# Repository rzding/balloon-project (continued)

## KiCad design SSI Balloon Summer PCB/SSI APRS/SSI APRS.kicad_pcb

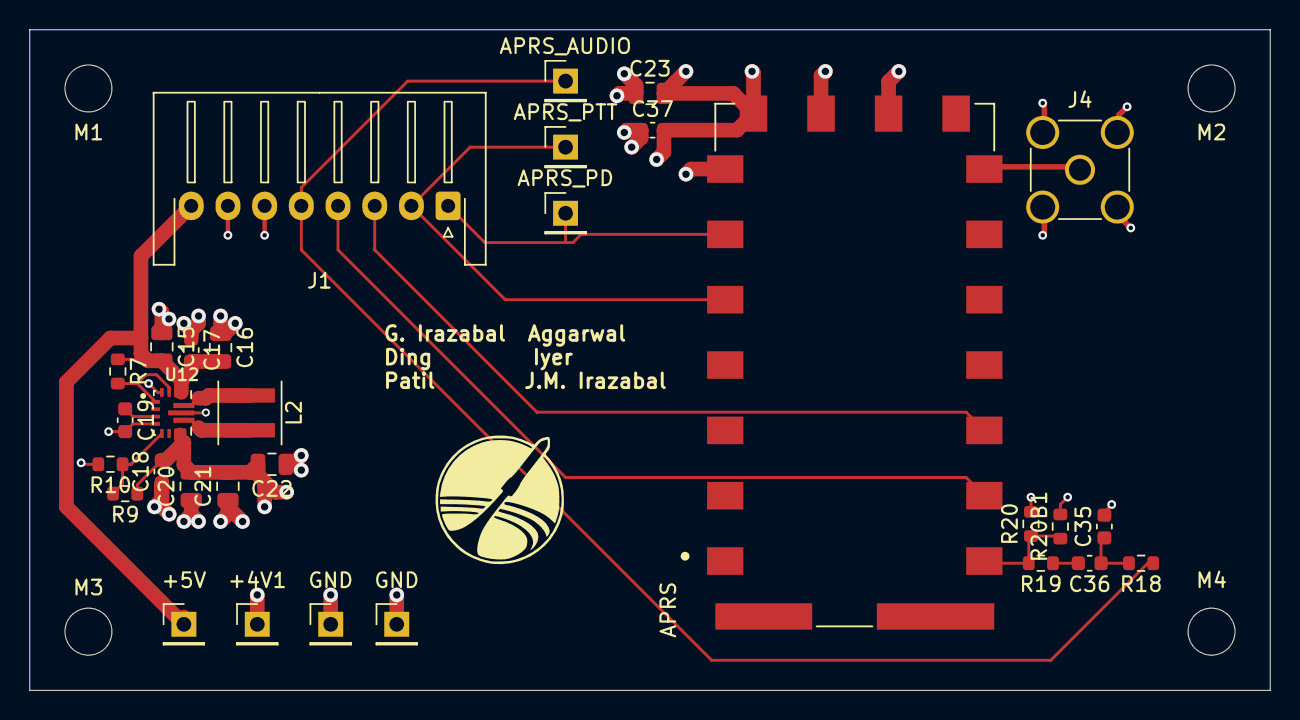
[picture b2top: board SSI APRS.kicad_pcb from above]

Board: 4 copper layers, 84.5 x 45.0 mm, 35 parts (0 on the bottom side), 17 nets.

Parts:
+4V1, +5V: Conn_01x01; PinHeader_1x01_P2.54mm_Vertical
APRS: DRA818V; DORJI_DRA818V
APRS_AUDIO: Conn_01x01; PinHeader_1x01_P2.54mm_Vertical
APRS_PD: Conn_01x01; PinHeader_1x01_P2.54mm_Vertical
APRS_PTT: Conn_01x01; PinHeader_1x01_P2.54mm_Vertical
C15, C16, C23: 10uF; C_0805_2012Metric
C17, C18: 10uF; C_0603_1608Metric
C19, C36, C37: 100nF; C_0603_1608Metric
C20, C21, C22: 22uF; C_0805_2012Metric
C35: 10nF; C_0603_1608Metric
GND: Conn_01x01; PinHeader_1x01_P2.54mm_Vertical
GND#2: Conn_01x01; PinHeader_1x01_P2.54mm_Vertical
J1: Conn_01x08; JST_XH_S8B-XH-A-1_1x08_P2.50mm_Horizontal
J4: APRS antenna; SMA_Amphenol_901-144_Vertical
L2: 1.5 uH; L_Coilcraft_XxL4020
M1, M2, M3, M4: MountingHole_3.2mm_M3
R7, R19: 10k; R_0603_1608Metric
R9: 510k; R_0603_1608Metric
R10: 120k; R_0603_1608Metric
R18: 1k; R_0603_1608Metric
R20: 470; R_0603_1608Metric
R20B1: TBD; R_0603_1608Metric
U12: TPS63070RNMR; VREG_TPS63070RNMR

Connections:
+4V1: +4V1.1 (Pin_1_1), APRS.8 (VBAT), C18.2, C20.2, C21.2, C22.2, C23.2, C37.2, R9.1, U12.7_8 (VOUT)
+5V: +5V.1 (Pin_1_1), C15.2, C16.2, C17.2, J1.8, R7.1, U12.12_13 (VIN)
/APRS_AUDIO: APRS_AUDIO.1 (Pin_1_1), J1.5, R18.1
/APRS_PD: APRS.6 (PD), APRS_PD.1 (Pin_1_1), J1.1
/APRS_PTT: APRS.5 (PTT), APRS_PTT.1 (Pin_1_1), J1.2
/APRS_RX: APRS.16 (RXD), J1.3
/APRS_TX: APRS.17 (TXD), J1.4
GND: APRS.7 (H/L), APRS.9 (GND), APRS.10 (GND), C15.1, C16.1, C17.1, C18.1, C19.2, C20.1, C21.1, C22.1, C23.1, C35.2, C37.1, GND.1 (Pin_1_1), GND#2.1 (Pin_1_1), J1.6, J1.7, J4.2 (Ext), R10.2, R20.2, R20B1.2, U12.4 (GND), U12.10 (PGND), U12.15 (VSEL)
unnamed: C35.1, C36.1, R18.2
unnamed: C36.2, R19.1
unnamed: APRS.12 (ANT), J4.1 (In)
unnamed: APRS.18 (MIC_IN), R19.2, R20.1, R20B1.1
unnamed: R7.2, U12.1 (PS/SYNC), U12.14 (EN)
unnamed: R9.2, R10.1, U12.5 (FB)
unnamed: L2.1, U12.11 (L1)
unnamed: L2.2, U12.9 (L2)
unnamed: C19.1, U12.3 (VAUX)

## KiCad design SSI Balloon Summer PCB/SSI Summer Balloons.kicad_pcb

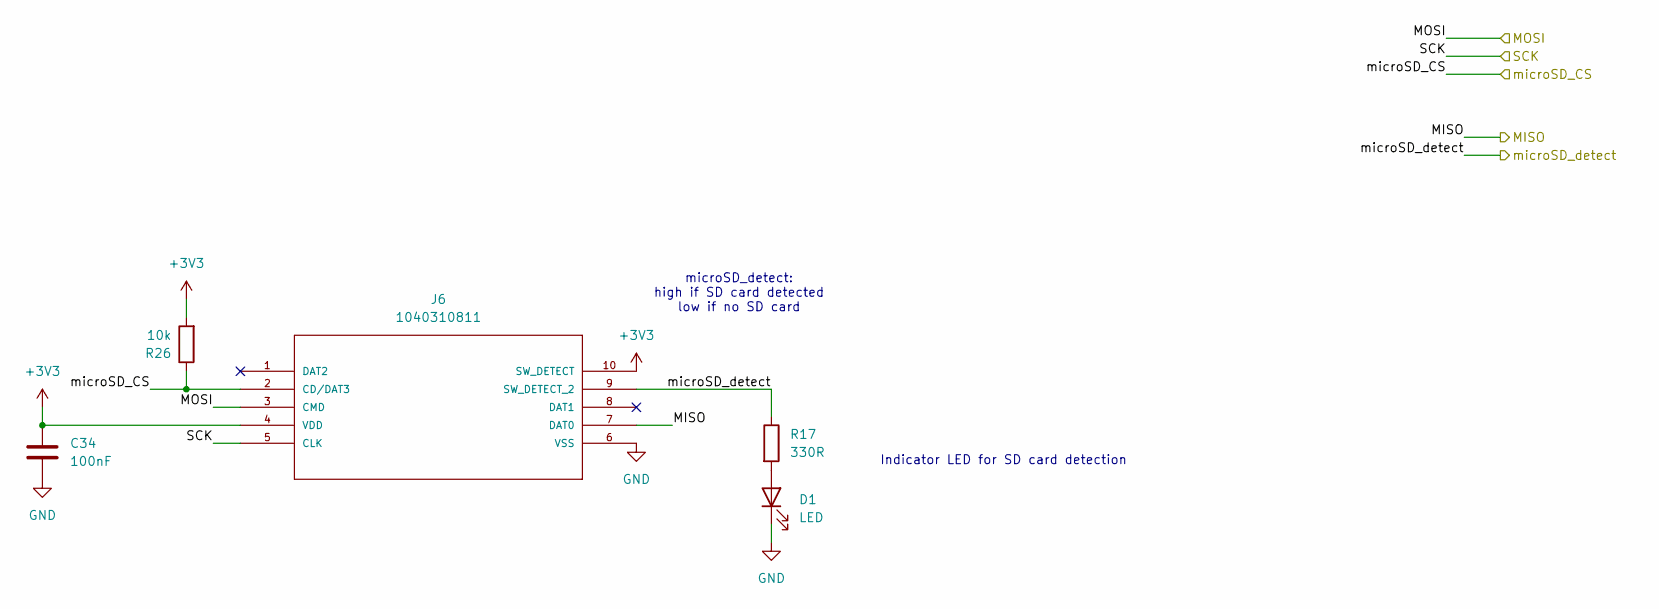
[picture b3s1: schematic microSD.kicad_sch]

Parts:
C34: 100nF
D1: LED
J6: 1040310811; 104031-0811_MOL; MANUFACTURER_PART_NUMBER 1040310811
R17: 330R
R26: 10k

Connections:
+3V3: C34.1, J6.4 (VDD), J6.10 (SW_DETECT), R26.2; also elsewhere on the board
/MCU (STM)/MISO: J6.7 (DAT0); also elsewhere on the board
/MCU (STM)/MOSI: J6.3 (CMD); also elsewhere on the board
/MCU (STM)/SCK: J6.5 (CLK); also elsewhere on the board
/MCU (STM)/microSD_CS: J6.2 (CD/DAT3), R26.1; also elsewhere on the board
/MCU (STM)/microSD_detect: J6.9 (SW_DETECT_2), R17.1; also elsewhere on the board
GND: C34.2, D1.1 (K), J6.6 (VSS); also elsewhere on the board
unnamed: D1.2 (A), R17.2

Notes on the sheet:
microSD_detect: high if SD card detected low if no SD card
Indicator LED for SD card detection

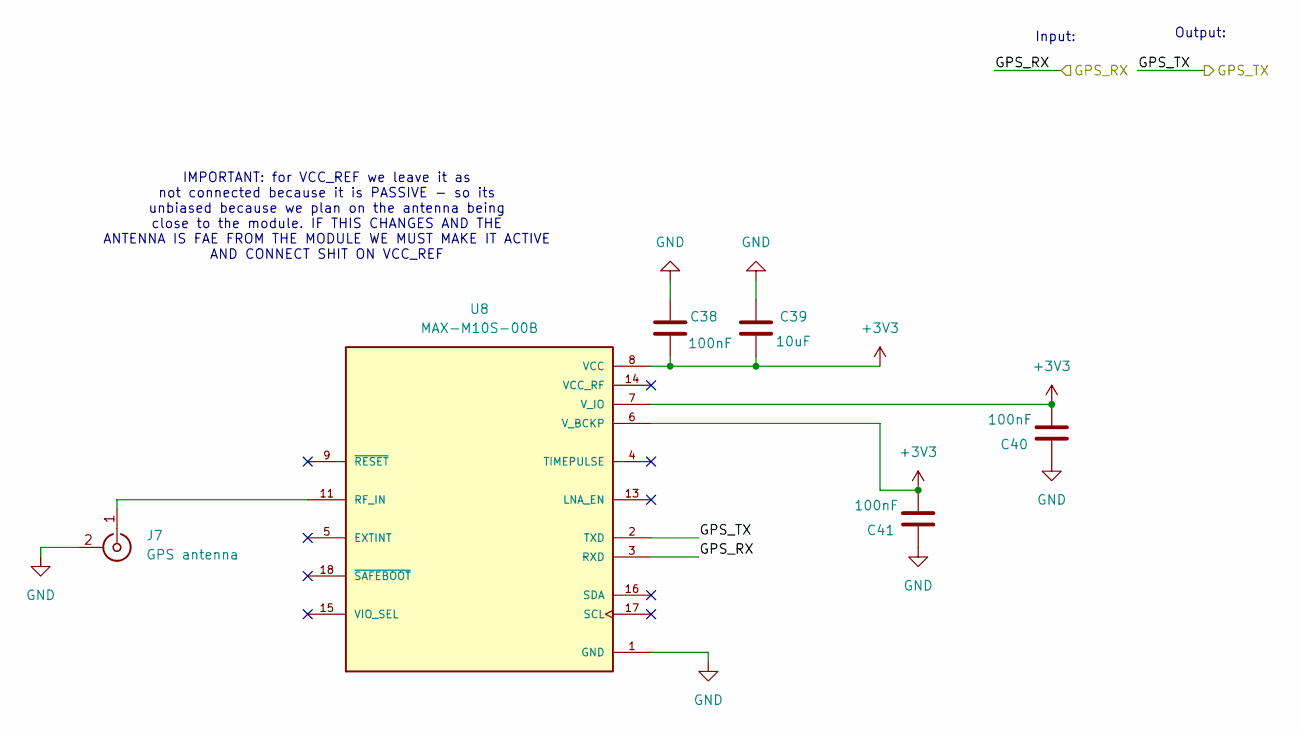
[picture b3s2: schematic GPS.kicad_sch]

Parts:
C38, C40, C41: 100nF; C_0603_1608Metric
C39: 10uF; C_0805_2012Metric
J7: GPS antenna; U.FL_Hirose_U.FL-R-SMT-1_Vertical
U8: MAX-M10S-00B; XCVR_MAX-M10S-00B; PARTREV C1

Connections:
+3V3: C38.2, C39.2, C40.2, C41.2, U8.6 (V_BCKP), U8.7 (V_IO), U8.8 (VCC); also elsewhere on the board
/GPS/GPS_RX: U8.3 (RXD); also elsewhere on the board
/GPS/GPS_TX: U8.2 (TXD); also elsewhere on the board
GND: C38.1, C39.1, C40.1, C41.1, J7.2 (Ext), U8.1 (GND), U8.10 (GND), U8.12 (GND); also elsewhere on the board
unnamed: J7.1 (In), U8.11 (RF_IN)

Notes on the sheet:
IMPORTANT: for VCC_REF we leave it as not connected because it is PASSIVE - so its unbiased because we plan on the antenna being close to the module. IF THIS CHANGES AND THE ANTENNA IS FAE FROM THE MODULE WE MUST MAKE IT ACTIVE AND CONNECT SHIT ON VCC_REF
Output:
Input:

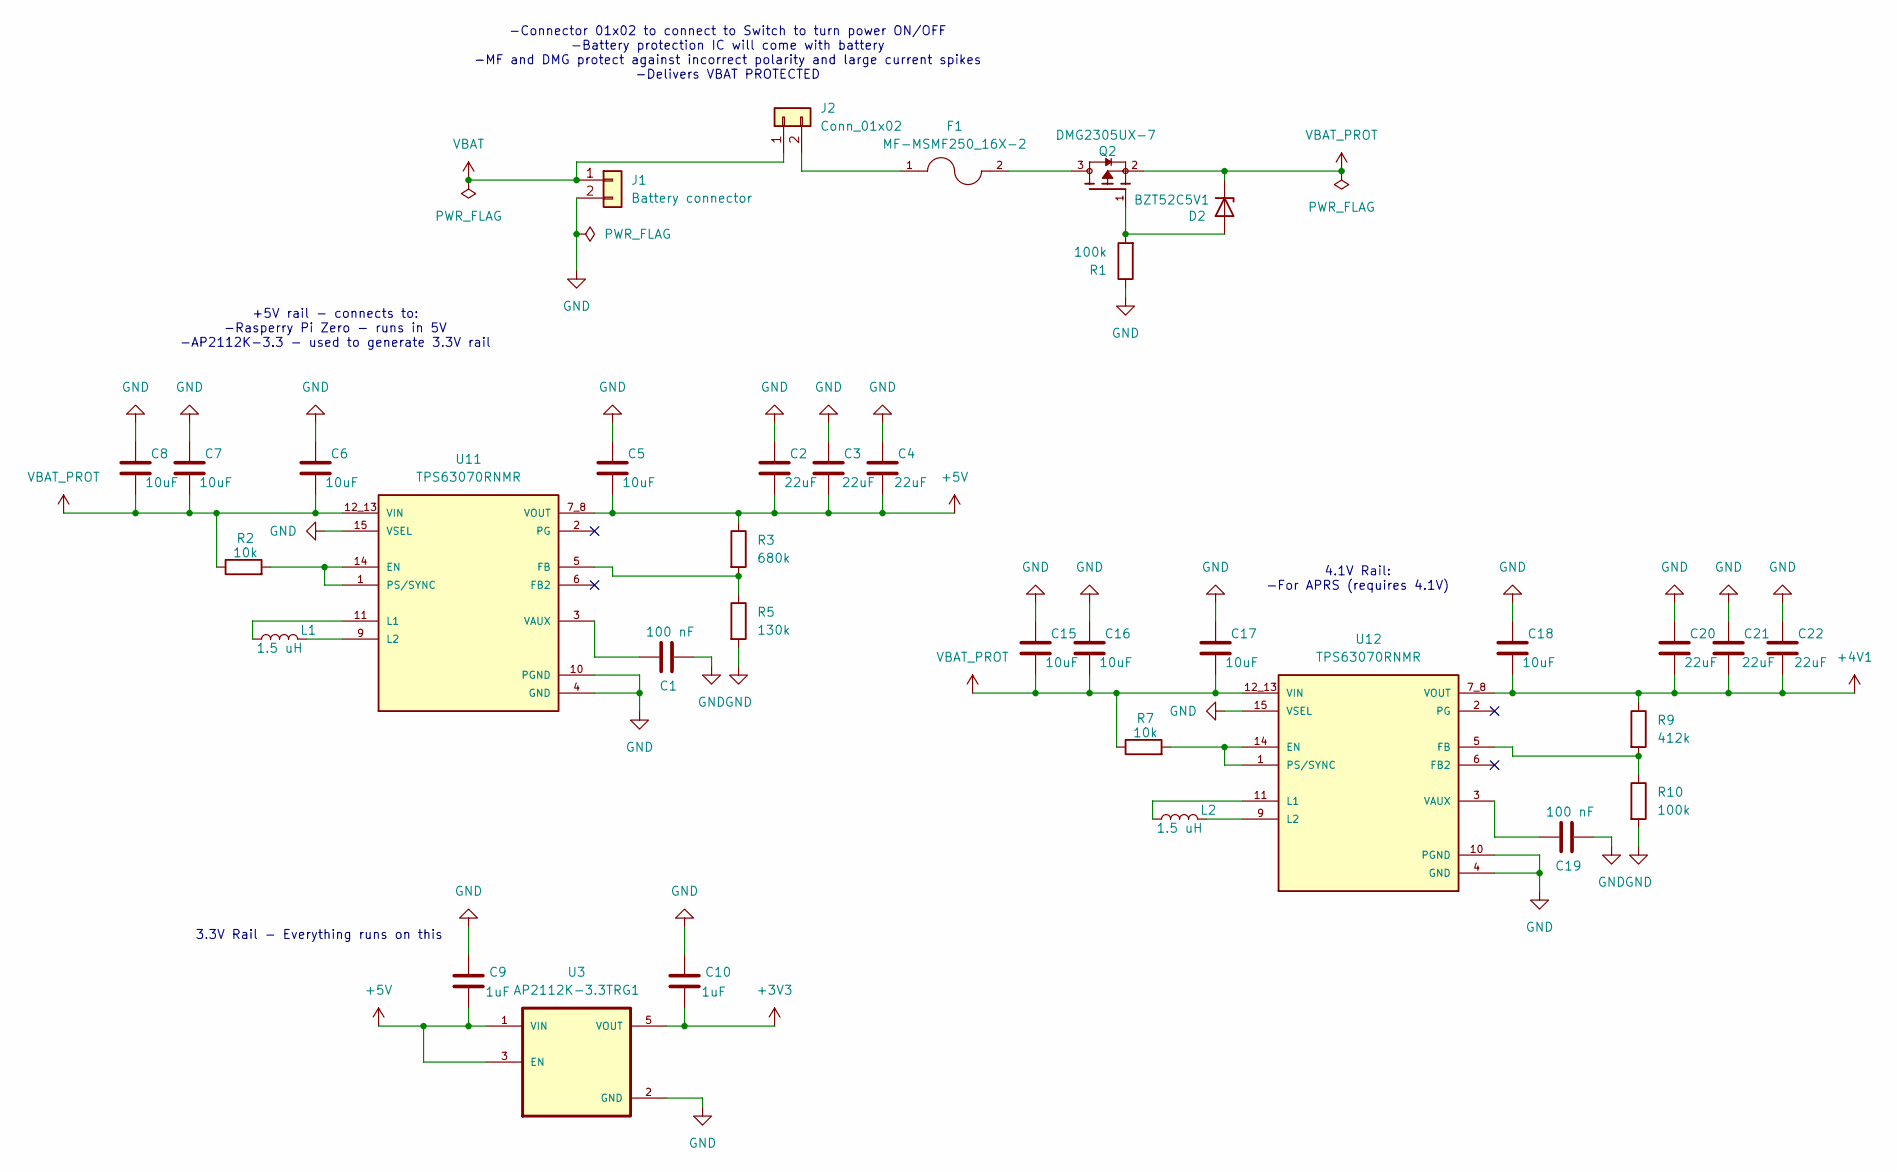
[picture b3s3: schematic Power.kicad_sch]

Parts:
C1, C19: 100 nF; C_0603_1608Metric
C2, C3, C4, C20, C21, C22: 22uF; C_0805_2012Metric
C5, C6, C17, C18: 10uF; C_0603_1608Metric
C7, C8, C15, C16: 10uF; C_0805_2012Metric
C9, C10: 1uF; C_0603_1608Metric
D2: BZT52C5V1; D_SOD-123
F1: MF-MSMF250_16X-2; FUSER_MF-MSMF250_16X-2
J1: Battery connector; JST_XH_B2B-XH-A_1x02_P2.50mm_Vertical
J2: Conn_01x02; JST_PH_B2B-PH-K_1x02_P2.00mm_Vertical
L1, L2: 1.5 uH; L_Coilcraft_XxL4020
Q2: DMG2305UX-7; SOT91P240X110-3N_DMG2305UX-7; PARTREV 09/2018
R1, R10: 100k; R_0603_1608Metric
R2, R7: 10k; R_0603_1608Metric
R3: 680k; R_0603_1608Metric
R5: 130k; R_0603_1608Metric
R9: 412k; R_0603_1608Metric
U3: AP2112K-3.3TRG1; SOT95P285X140-5N; PARTREV 2-2
U11, U12: TPS63070RNMR; VREG_TPS63070RNMR; PARTREV B

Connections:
+3V3: C10.2, U3.5 (VOUT); also elsewhere on the board
+4V1: C18.2, C20.2, C21.2, C22.2, R9.1, U12.7_8 (VOUT); also elsewhere on the board
+5V: C2.2, C3.2, C4.2, C5.2, C9.2, R3.1, U3.1 (VIN), U3.3 (EN), U11.7_8 (VOUT); also elsewhere on the board
GND: C1.2, C2.1, C3.1, C4.1, C5.1, C6.1, C7.1, C8.1, C9.1, C10.1, C15.1, C16.1, C17.1, C18.1, C19.2, C20.1, C21.1, C22.1, J1.2, R1.1, R5.2, R10.2, U3.2 (GND), U11.4 (GND), U11.10 (PGND), U11.15 (VSEL), U12.4 (GND), U12.10 (PGND), U12.15 (VSEL); also elsewhere on the board
unnamed: D2.2 (A), Q2.1, R1.2
unnamed: F1.2, Q2.3
unnamed: F1.1, J2.2
unnamed: R2.2, U11.1 (PS/SYNC), U11.14 (EN)
unnamed: R3.2, R5.1, U11.5 (FB)
unnamed: L1.1, U11.11 (L1)
unnamed: L1.2, U11.9 (L2)
unnamed: C1.1, U11.3 (VAUX)
unnamed: R7.2, U12.1 (PS/SYNC), U12.14 (EN)
unnamed: R9.2, R10.1, U12.5 (FB)
unnamed: L2.1, U12.11 (L1)
unnamed: L2.2, U12.9 (L2)
unnamed: C19.1, U12.3 (VAUX)
VBAT: J1.1, J2.1
VBAT_PROT: C6.2, C7.2, C8.2, C15.2, C16.2, C17.2, D2.1 (K), Q2.2, R2.1, R7.1, U11.12_13 (VIN), U12.12_13 (VIN)

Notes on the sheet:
-Connector 01x02 to connect to Switch to turn power ON/OFF -Battery protection IC will come with battery -MF and DMG protect against incorrect polarity and large current spikes -Delivers VBAT PROTECTED
4.1V Rail: -For APRS (requires 4.1V)
3.3V Rail - Everything runs on this
+5V rail - connects to: -Rasperry Pi Zero - runs in 5V -AP2112K-3.3 - used to generate 3.3V rail

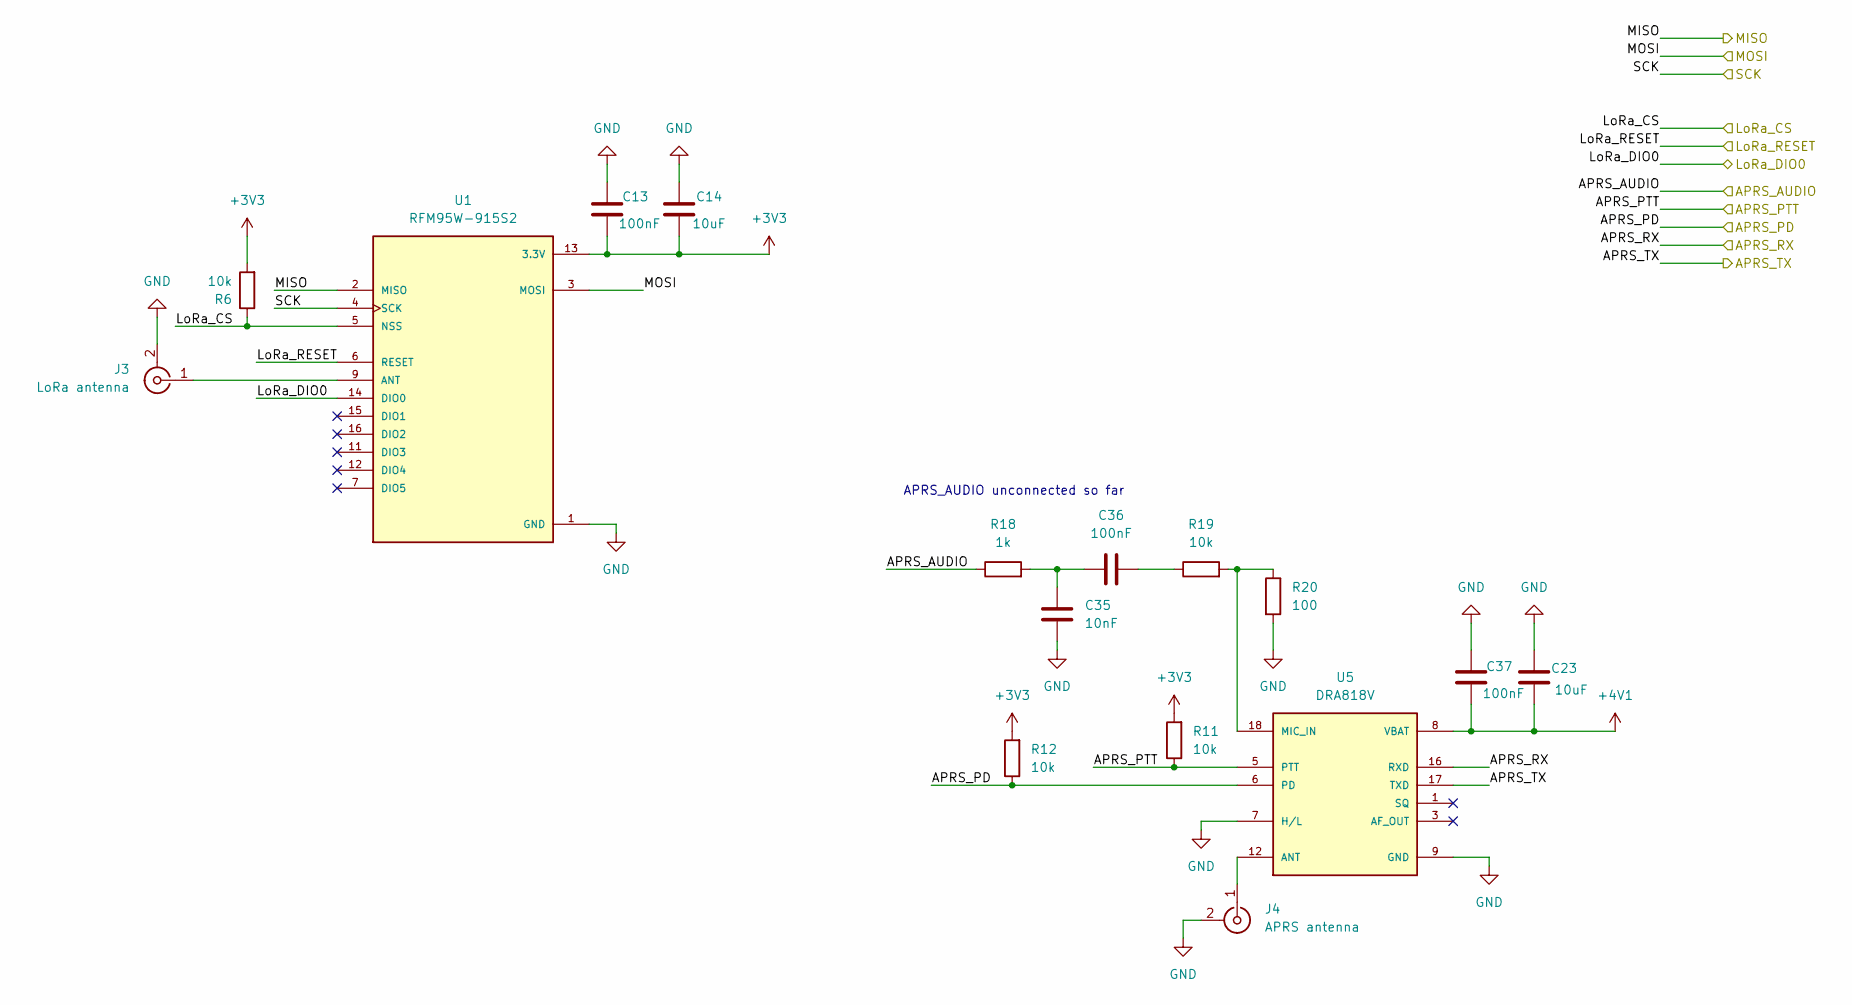
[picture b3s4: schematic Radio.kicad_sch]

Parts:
C13, C36, C37: 100nF; C_0603_1608Metric
C14, C23: 10uF; C_0805_2012Metric
C35: 10nF; C_0603_1608Metric
J3: LoRa antenna; U.FL_Hirose_U.FL-R-SMT-1_Vertical
J4: APRS antenna; U.FL_Hirose_U.FL-R-SMT-1_Vertical
R6, R11, R12, R19: 10k; R_0603_1608Metric
R18: 1k; R_0603_1608Metric
R20: 100; R_0603_1608Metric
U1: RFM95W-915S2; XCVR_RFM95W-915S2
U5: DRA818V; DORJI_DRA818V; PART_REV 1.23

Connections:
+3V3: C13.2, C14.2, R6.2, R11.2, R12.2, U1.13 (3.3V); also elsewhere on the board
+4V1: C23.2, C37.2, U5.8 (VBAT); also elsewhere on the board
/MCU (STM)/APRS_AUDIO: R18.1; also elsewhere on the board
/MCU (STM)/APRS_PD: R12.1, U5.6 (PD); also elsewhere on the board
/MCU (STM)/APRS_PTT: R11.1, U5.5 (PTT); also elsewhere on the board
/MCU (STM)/APRS_RX: U5.16 (RXD); also elsewhere on the board
/MCU (STM)/APRS_TX: U5.17 (TXD); also elsewhere on the board
/MCU (STM)/LoRa_CS: R6.1, U1.5 (NSS); also elsewhere on the board
/MCU (STM)/LoRa_DIO0: U1.14 (DIO0); also elsewhere on the board
/MCU (STM)/LoRa_RESET: U1.6 (RESET); also elsewhere on the board
/MCU (STM)/MISO: U1.2 (MISO); also elsewhere on the board
/MCU (STM)/MOSI: U1.3 (MOSI); also elsewhere on the board
/MCU (STM)/SCK: U1.4 (SCK); also elsewhere on the board
GND: C13.1, C14.1, C23.1, C35.2, C37.1, J3.2 (Ext), J4.2 (Ext), R20.2, U1.1 (GND), U1.8 (GND), U1.10 (GND), U5.7 (H/L), U5.9 (GND), U5.10 (GND); also elsewhere on the board
unnamed: C35.1, C36.1, R18.2
unnamed: C36.2, R19.1
unnamed: J3.1 (In), U1.9 (ANT)
unnamed: J4.1 (In), U5.12 (ANT)
unnamed: R19.2, R20.1, U5.18 (MIC_IN)

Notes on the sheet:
APRS_AUDIO unconnected so far

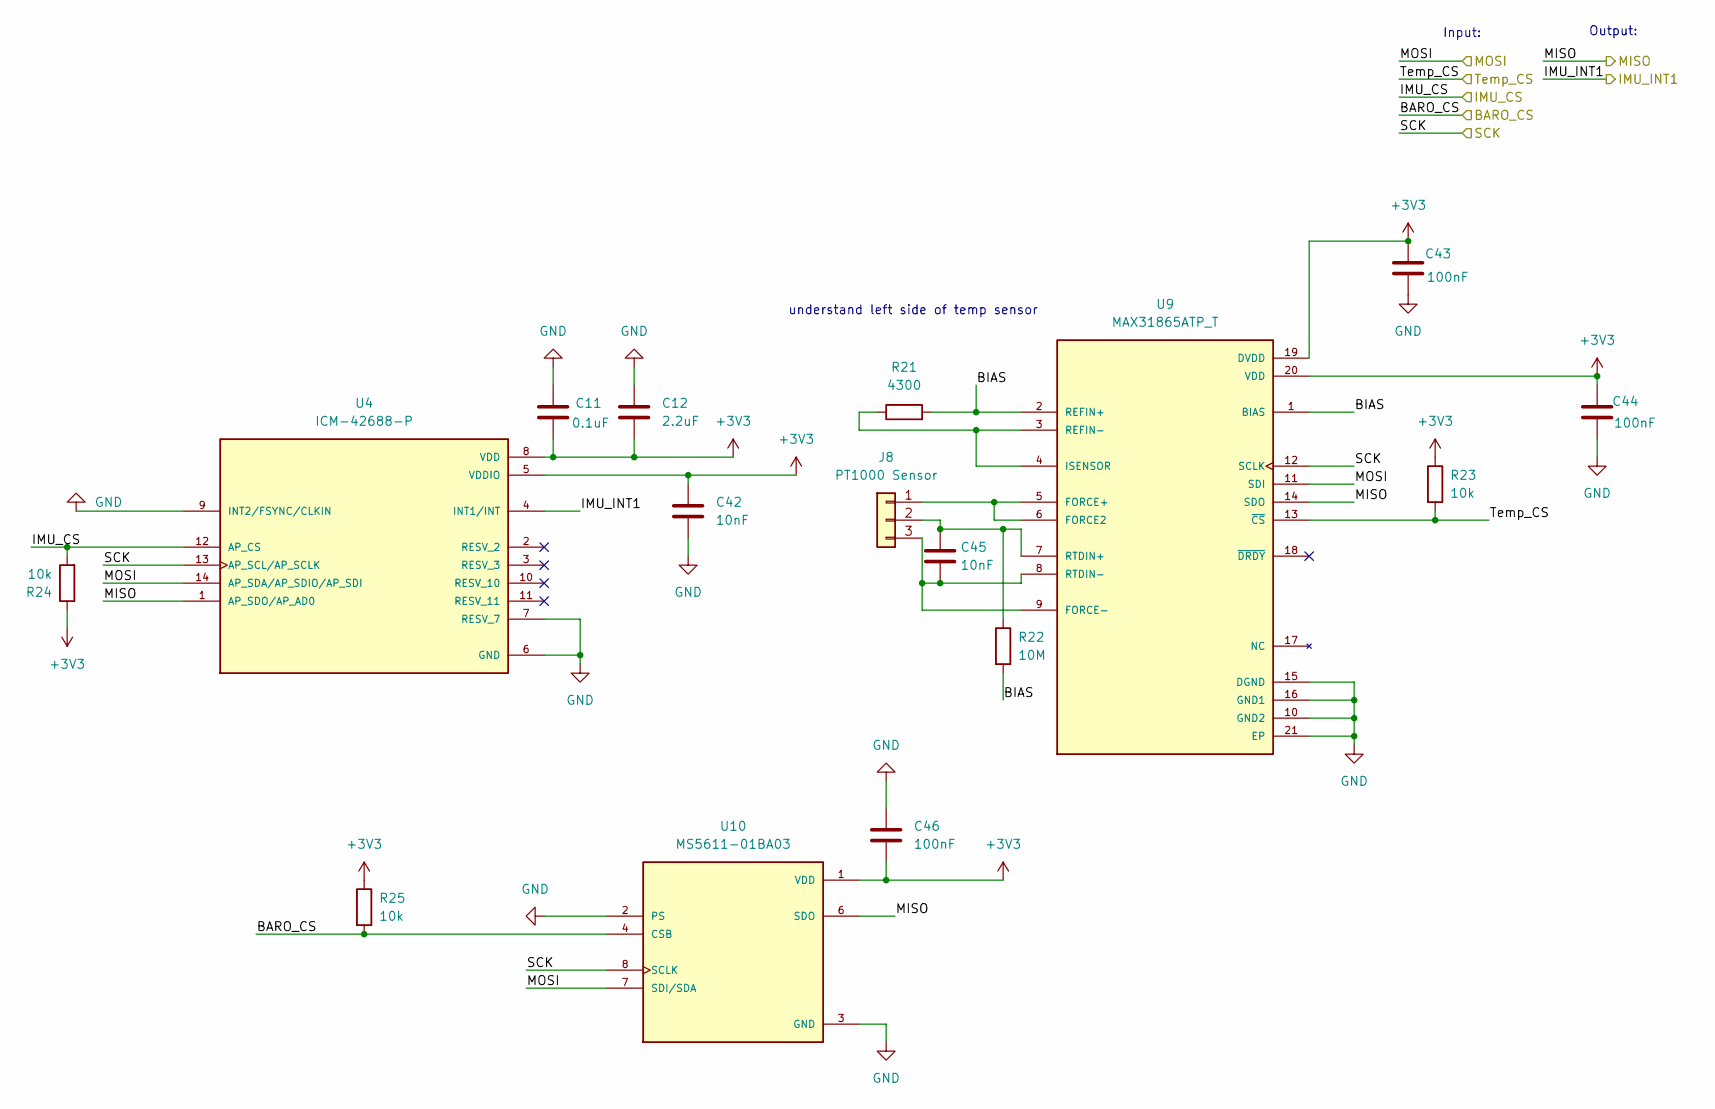
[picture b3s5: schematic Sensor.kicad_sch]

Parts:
C11: 0.1uF; C_0603_1608Metric
C12: 2.2uF; C_0603_1608Metric
C42, C45: 10nF; C_0603_1608Metric
C43, C44, C46: 100nF; C_0603_1608Metric
J8: PT1000 Sensor; JST_PH_B3B-PH-K_1x03_P2.00mm_Vertical
R21: 4300; R_0603_1608Metric
R22: 10M; R_0603_1608Metric
R23, R24, R25: 10k; R_0603_1608Metric
U4: ICM-42688-P; PQFN50P300X250X97-14N; PARTREV 1.2
U9: MAX31865ATP_T; QFN65P500X500X80-21N; PARTREV 3
U10: MS5611-01BA03; SON125P500X300X100-8N; PARTREV 06/2017

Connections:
+3V3: C11.2, C12.2, C42.1, C43.1, C44.1, C46.2, R23.1, R24.1, R25.1, U4.5 (VDDIO), U4.8 (VDD), U9.19 (DVDD), U9.20 (VDD), U10.1 (VDD); also elsewhere on the board
/MCU (STM)/BARO_CS: R25.2, U10.4 (CSB), U10.5 (CSB); also elsewhere on the board
/MCU (STM)/IMU_CS: R24.2, U4.12 (AP_CS); also elsewhere on the board
/MCU (STM)/IMU_INT1: U4.4 (INT1/INT); also elsewhere on the board
/MCU (STM)/MISO: U4.1 (AP_SDO/AP_AD0), U9.14 (SDO), U10.6 (SDO); also elsewhere on the board
/MCU (STM)/MOSI: U4.14 (AP_SDA/AP_SDIO/AP_SDI), U9.11 (SDI), U10.7 (SDI/SDA); also elsewhere on the board
/MCU (STM)/SCK: U4.13 (AP_SCL/AP_SCLK), U9.12 (SCLK), U10.8 (SCLK); also elsewhere on the board
/MCU (STM)/Temp_CS: R23.2, U9.13 (~CS); also elsewhere on the board
/Sensor/BIAS: R21.2, R22.2, U9.1 (BIAS), U9.2 (REFIN+)
GND: C11.1, C12.1, C42.2, C43.2, C44.2, C46.1, U4.6 (GND), U4.7 (RESV_7), U4.9 (INT2/FSYNC/CLKIN), U9.10 (GND2), U9.15 (DGND), U9.16 (GND1), U9.21 (EP), U10.2 (PS), U10.3 (GND); also elsewhere on the board
unnamed: J8.1, U9.5 (FORCE+), U9.6 (FORCE2)
unnamed: C45.1, J8.2, R22.1, U9.7 (RTDIN+)
unnamed: C45.2, J8.3, U9.8 (RTDIN-), U9.9 (FORCE-)
unnamed: R21.1, U9.3 (REFIN-), U9.4 (ISENSOR)

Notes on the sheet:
Output:
understand left side of temp sensor
Input:

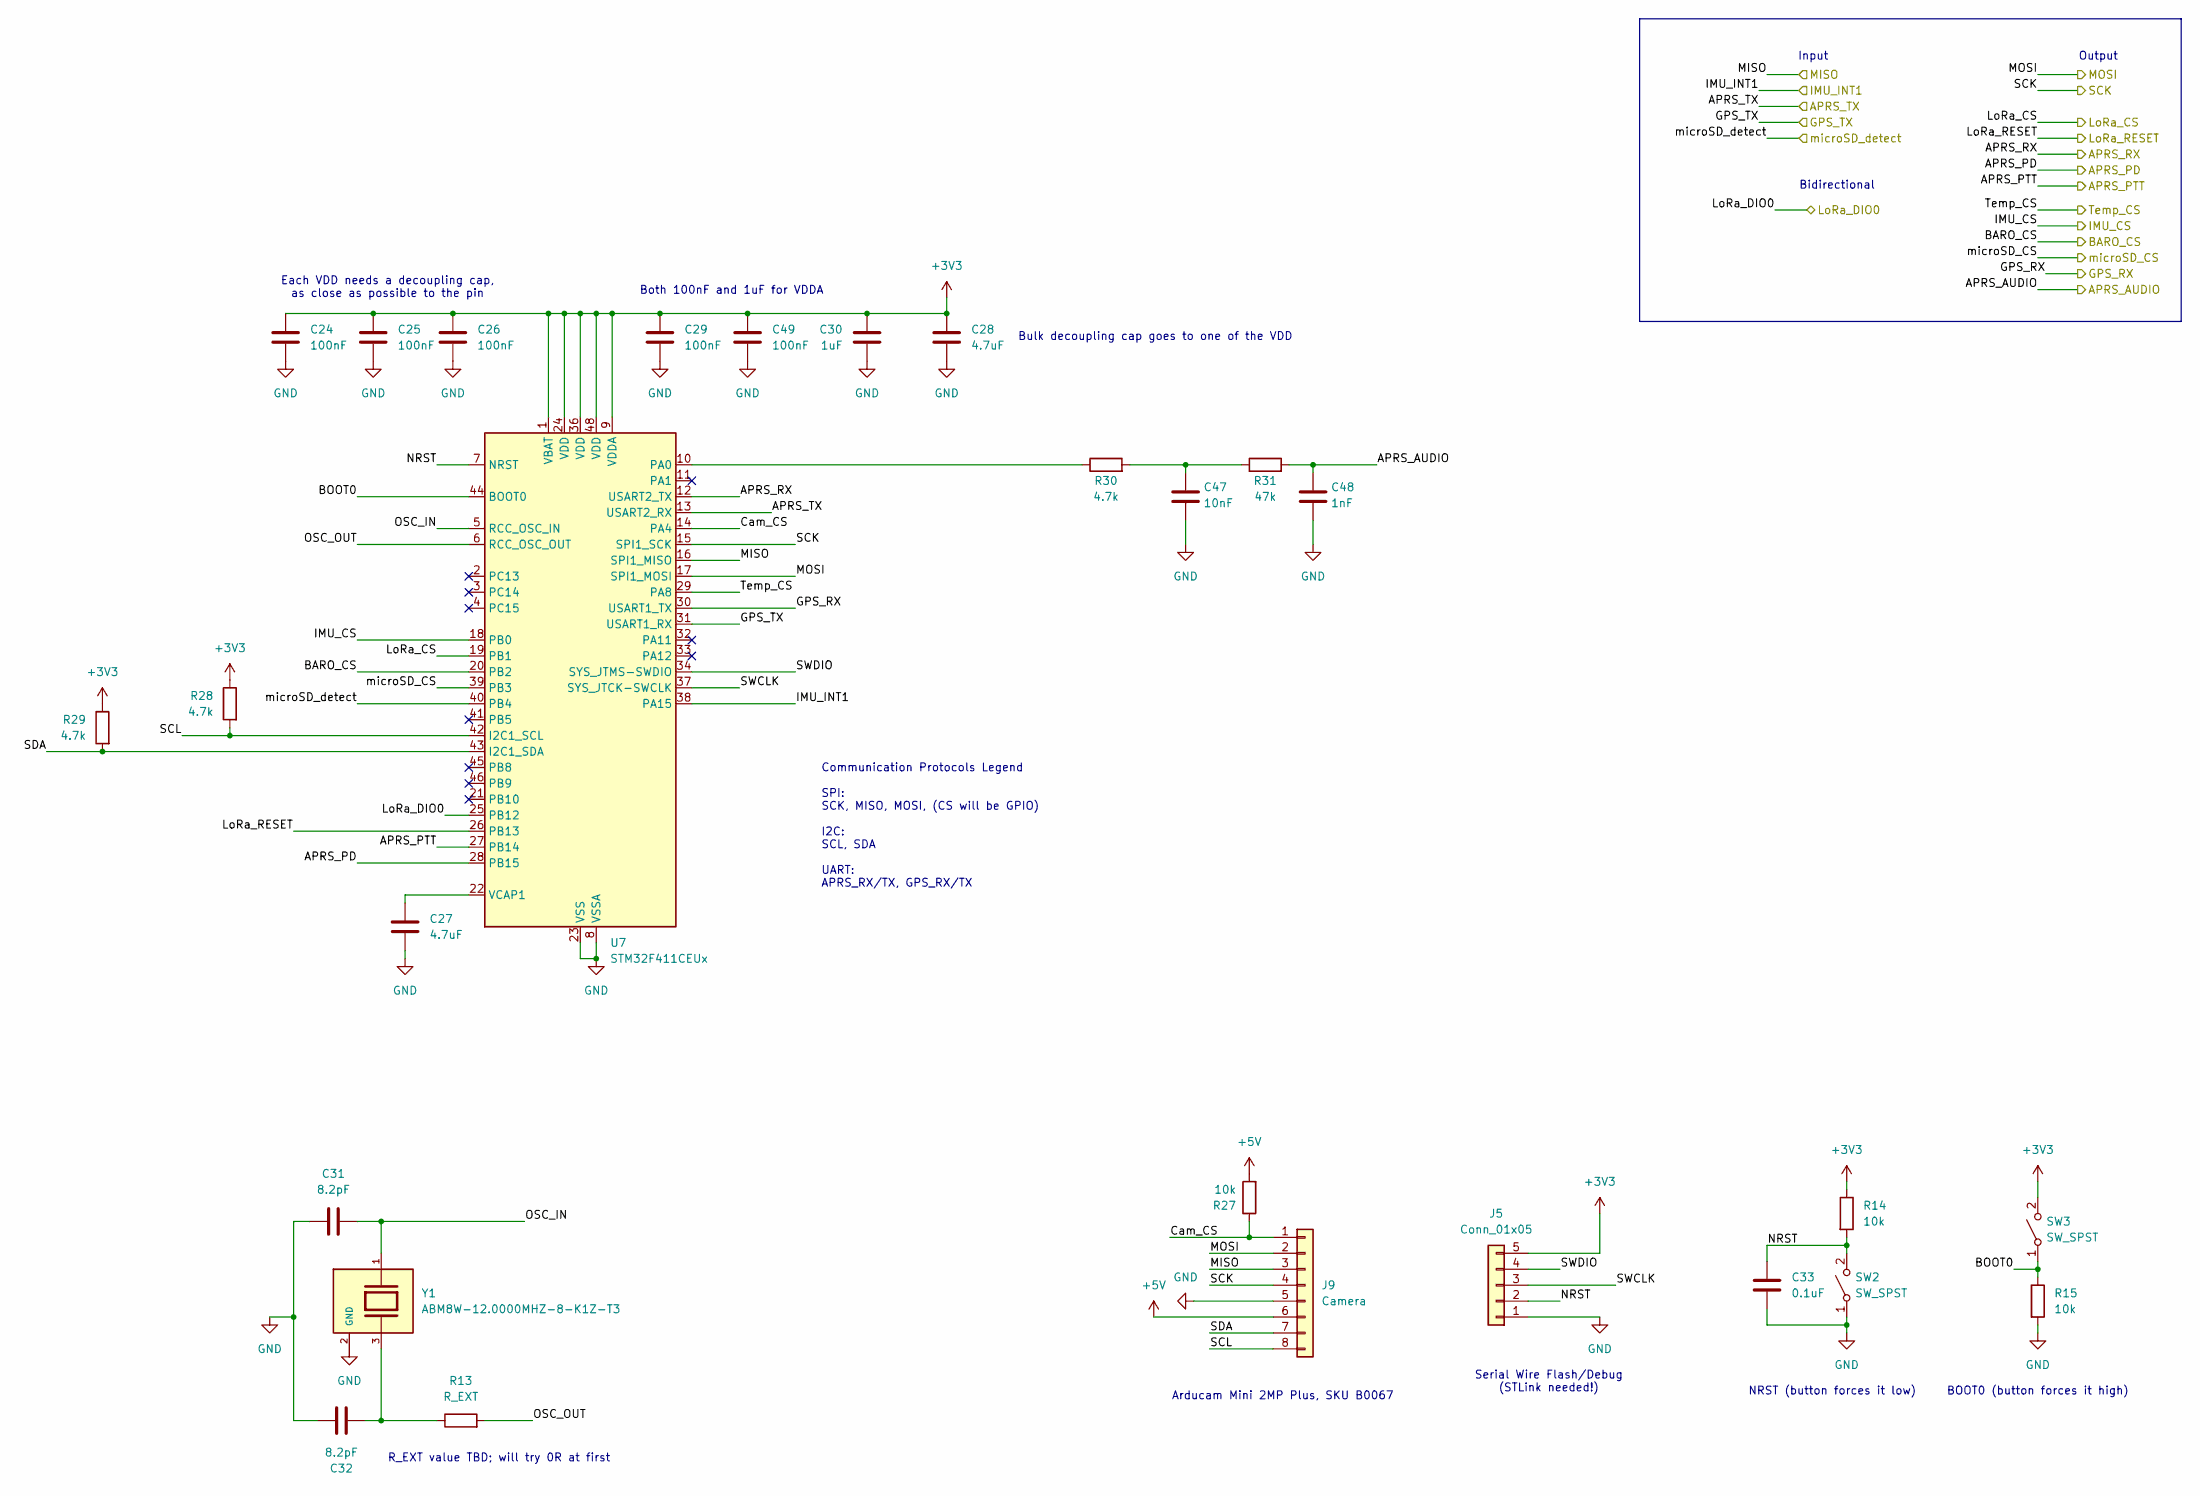
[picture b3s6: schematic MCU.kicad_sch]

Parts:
C24, C25, C26, C29, C49: 100nF; C_0603_1608Metric
C27, C28: 4.7uF; C_0805_2012Metric
C30: 1uF; C_0603_1608Metric
C31, C32: 8.2pF; C_0603_1608Metric
C33: 0.1uF; C_0603_1608Metric
C47: 10nF; C_0603_1608Metric
C48: 1nF; C_0603_1608Metric
J5: Conn_01x05; PinHeader_1x05_P2.54mm_Vertical
J9: Camera; PinHeader_1x08_P2.54mm_Vertical
R13: R_EXT; R_0603_1608Metric
R14, R15, R27: 10k; R_0603_1608Metric
R28, R29, R30: 4.7k; R_0603_1608Metric
R31: 47k; R_0603_1608Metric
SW2, SW3: SW_SPST; SW_Push_1P1T-MP_NO_Horizontal_Alps_SKRTLAE010
U7: STM32F411CEUx; QFN-48-1EP_7x7mm_P0.5mm_EP5.6x5.6mm
Y1: ABM8W-12.0000MHZ-8-K1Z-T3; XTAL_ABM8W-12.0000MHZ-8-K1Z-T3; PARTREV 08.09.2018; DigiKey_Part_Number 535-14010-1-ND

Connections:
+3V3: C24.1, C25.1, C26.1, C28.1, C29.1, C30.1, C49.1, J5.5, R14.1, R28.1, R29.1, SW3.2 (B), U7.1 (VBAT), U7.9 (VDDA), U7.24 (VDD), U7.36 (VDD), U7.48 (VDD); also elsewhere on the board
+5V: J9.6, R27.2; also elsewhere on the board
/GPS/GPS_RX: U7.30 (USART1_TX); also elsewhere on the board
/GPS/GPS_TX: U7.31 (USART1_RX); also elsewhere on the board
/MCU (STM)/APRS_AUDIO: C48.1, R31.2; also elsewhere on the board
/MCU (STM)/APRS_PD: U7.28 (PB15); also elsewhere on the board
/MCU (STM)/APRS_PTT: U7.27 (PB14); also elsewhere on the board
/MCU (STM)/APRS_RX: U7.12 (USART2_TX); also elsewhere on the board
/MCU (STM)/APRS_TX: U7.13 (USART2_RX); also elsewhere on the board
/MCU (STM)/BARO_CS: U7.20 (PB2); also elsewhere on the board
/MCU (STM)/BOOT0: R15.1, SW3.1 (A), U7.44 (BOOT0)
/MCU (STM)/Cam_CS: J9.1, R27.1, U7.14 (PA4)
/MCU (STM)/IMU_CS: U7.18 (PB0); also elsewhere on the board
/MCU (STM)/IMU_INT1: U7.38 (PA15); also elsewhere on the board
/MCU (STM)/LoRa_CS: U7.19 (PB1); also elsewhere on the board
/MCU (STM)/LoRa_DIO0: U7.25 (PB12); also elsewhere on the board
/MCU (STM)/LoRa_RESET: U7.26 (PB13); also elsewhere on the board
/MCU (STM)/MISO: J9.3, U7.16 (SPI1_MISO); also elsewhere on the board
/MCU (STM)/MOSI: J9.2, U7.17 (SPI1_MOSI); also elsewhere on the board
/MCU (STM)/NRST: C33.1, J5.2, R14.2, SW2.2 (B), U7.7 (NRST)
/MCU (STM)/OSC_IN: C31.2, U7.5 (RCC_OSC_IN), Y1.1
/MCU (STM)/OSC_OUT: R13.2, U7.6 (RCC_OSC_OUT)
/MCU (STM)/SCK: J9.4, U7.15 (SPI1_SCK); also elsewhere on the board
/MCU (STM)/SCL: J9.8, R28.2, U7.42 (I2C1_SCL)
/MCU (STM)/SDA: J9.7, R29.2, U7.43 (I2C1_SDA)
/MCU (STM)/SWCLK: J5.3, U7.37 (SYS_JTCK-SWCLK)
/MCU (STM)/SWDIO: J5.4, U7.34 (SYS_JTMS-SWDIO)
/MCU (STM)/Temp_CS: U7.29 (PA8); also elsewhere on the board
/MCU (STM)/microSD_CS: U7.39 (PB3); also elsewhere on the board
/MCU (STM)/microSD_detect: U7.40 (PB4); also elsewhere on the board
GND: C24.2, C25.2, C26.2, C27.2, C28.2, C29.2, C30.2, C31.1, C32.1, C33.2, C47.2, C48.2, C49.2, J5.1, J9.5, R15.2, SW2.1 (A), U7.8 (VSSA), U7.23 (VSS), U7.35 (VSS), U7.47 (VSS), U7.49 (VSS), Y1.2 (GND), Y1.4 (GND); also elsewhere on the board
unnamed: C32.2, R13.1, Y1.3
unnamed: C47.1, R30.2, R31.1
unnamed: R30.1, U7.10 (PA0)
unnamed: C27.1, U7.22 (VCAP1)

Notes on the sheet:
Bidirectional
NRST (button forces it low)
BOOT0 (button forces it high)
Output
Input
Communication Protocols Legend SPI: SCK, MISO, MOSI, (CS will be GPIO) I2C: SCL, SDA UART: APRS_RX/TX, GPS_RX/TX
R_EXT value TBD; will try 0R at first
Both 100nF and 1uF for VDDA
Each VDD needs a decoupling cap, as close as possible to the pin
Arducam Mini 2MP Plus, SKU B0067
Serial Wire Flash/Debug (STLink needed!)
Bulk decoupling cap goes to one of the VDD

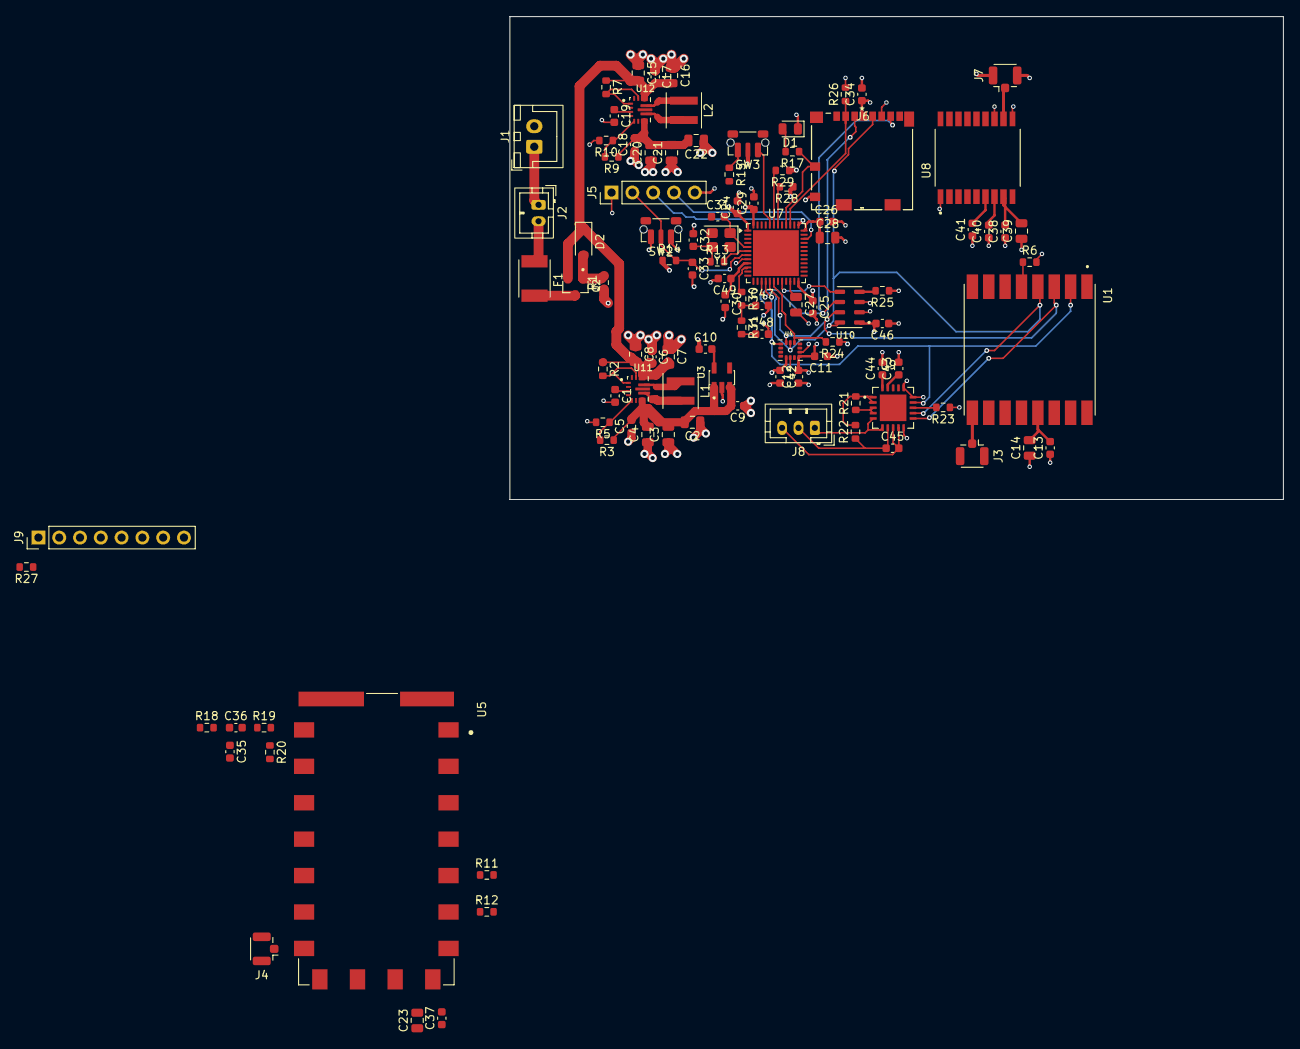
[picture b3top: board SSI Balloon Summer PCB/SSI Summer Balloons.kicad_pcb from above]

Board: 4 copper layers, 94.5 x 59.0 mm, 105 parts (0 on the bottom side), 63 nets.

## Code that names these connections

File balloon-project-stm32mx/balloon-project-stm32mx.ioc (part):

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Mcu.Name=STM32F411C(C-E)Ux
Mcu.Package=UFQFPN48
Mcu.UserName=STM32F411CEUx
PA0-WKUP.GPIOParameters=GPIO_ModeDefaultPP,GPIO_Speed,GPIO_Label
PA0-WKUP.GPIO_Label=APRS_PWM
PA0-WKUP.GPIO_ModeDefaultPP=GPIO_MODE_AF_PP
PA0-WKUP.GPIO_Speed=GPIO_SPEED_FREQ_HIGH
PA0-WKUP.Signal=S_TIM2_CH1_ETR
PA10.GPIOParameters=GPIO_Speed,GPIO_PuPd
PA10.GPIO_PuPd=GPIO_PULLUP
PA10.GPIO_Speed=GPIO_SPEED_FREQ_LOW
PA10.Mode=Asynchronous
PA10.Signal=USART1_RX
PA13.Mode=Serial_Wire
PA13.Signal=SYS_JTMS-SWDIO
PA14.Mode=Serial_Wire
PA14.Signal=SYS_JTCK-SWCLK
PA15.GPIOParameters=GPIO_Label
PA15.GPIO_Label=IMU_INT1
PA15.Signal=GPXTI15
PA2.GPIOParameters=GPIO_Speed,GPIO_PuPd
PA2.GPIO_PuPd=GPIO_PULLUP
PA2.GPIO_Speed=GPIO_SPEED_FREQ_LOW
PA2.Mode=Asynchronous
PA2.Signal=USART2_TX
PA3.GPIOParameters=GPIO_Speed,GPIO_PuPd
PA3.GPIO_PuPd=GPIO_PULLUP
PA3.GPIO_Speed=GPIO_SPEED_FREQ_LOW
PA3.Mode=Asynchronous
PA3.Signal=USART2_RX
PA4.GPIOParameters=GPIO_Speed,PinState,GPIO_Label,GPIO_ModeDefaultOutputPP
PA4.GPIO_Label=Cam_CS
PA4.GPIO_ModeDefaultOutputPP=GPIO_MODE_OUTPUT_PP
PA4.GPIO_Speed=GPIO_SPEED_FREQ_HIGH
PA4.PinState=GPIO_PIN_SET
PA4.Signal=GPIO_Output
PA5.GPIOParameters=GPIO_Speed
PA5.GPIO_Speed=GPIO_SPEED_FREQ_HIGH
PA5.Mode=Full_Duplex_Master
PA5.Signal=SPI1_SCK
PA6.GPIOParameters=GPIO_Speed
PA6.GPIO_Speed=GPIO_SPEED_FREQ_HIGH
PA6.Mode=Full_Duplex_Master
PA6.Signal=SPI1_MISO
PA7.GPIOParameters=GPIO_Speed
PA7.GPIO_Speed=GPIO_SPEED_FREQ_HIGH
PA7.Mode=Full_Duplex_Master
PA7.Signal=SPI1_MOSI
PA8.GPIOParameters=GPIO_Speed,PinState,GPIO_Label
PA8.GPIO_Label=Temp_CS
PA8.GPIO_Speed=GPIO_SPEED_FREQ_HIGH
PA8.PinState=GPIO_PIN_SET
PA8.Signal=GPIO_Output
PA9.GPIOParameters=GPIO_Speed,GPIO_PuPd
PA9.GPIO_PuPd=GPIO_PULLUP
PA9.GPIO_Speed=GPIO_SPEED_FREQ_LOW
PA9.Mode=Asynchronous
PA9.Signal=USART1_TX
PB0.GPIOParameters=GPIO_Speed,PinState,GPIO_Label
PB0.GPIO_Label=IMU_CS
PB0.GPIO_Speed=GPIO_SPEED_FREQ_HIGH
PB0.PinState=GPIO_PIN_SET
PB0.Signal=GPIO_Output
PB1.GPIOParameters=GPIO_Speed,PinState,GPIO_Label
PB1.GPIO_Label=LoRa_CS
PB1.GPIO_Speed=GPIO_SPEED_FREQ_HIGH
PB1.PinState=GPIO_PIN_SET
PB1.Signal=GPIO_Output
PB12.GPIOParameters=GPIO_Label
PB12.GPIO_Label=LoRa_DIO0
PB12.Signal=GPXTI12
PB13.GPIOParameters=GPIO_Label
PB13.GPIO_Label=LoRa_RESET
PB13.Signal=GPIO_Output
PB14.GPIOParameters=GPIO_Label
PB14.GPIO_Label=APRS_PTT
PB14.Signal=GPIO_Output
PB15.GPIOParameters=GPIO_Label
PB15.GPIO_Label=APRS_PD
PB15.Signal=GPIO_Output
PB2.GPIOParameters=GPIO_Speed,PinState,GPIO_Label
PB2.GPIO_Label=BARO_CS
PB2.GPIO_Speed=GPIO_SPEED_FREQ_HIGH
PB2.PinState=GPIO_PIN_SET
PB2.Signal=GPIO_Output
PB3.GPIOParameters=GPIO_Speed,PinState,GPIO_Label
PB3.GPIO_Label=microSD_CS
PB3.GPIO_Speed=GPIO_SPEED_FREQ_HIGH
PB3.PinState=GPIO_PIN_SET
PB3.Signal=GPIO_Output
PB4.GPIOParameters=GPIO_PuPd,GPIO_Label
PB4.GPIO_Label=microSD_detect
PB4.GPIO_PuPd=GPIO_PULLUP
PB4.Signal=GPIO_Input
PB5.GPIOParameters=GPIO_Label
PB5.GPIO_Label=LED
PB5.Signal=GPIO_Output
PB6.GPIOParameters=GPIO_Speed
PB6.GPIO_Speed=GPIO_SPEED_FREQ_HIGH
PB6.Mode=I2C
PB6.Signal=I2C1_SCL
PB7.GPIOParameters=GPIO_Speed
PB7.GPIO_Speed=GPIO_SPEED_FREQ_HIGH
PB7.Mode=I2C
PB7.Signal=I2C1_SDA
PH0\ -\ OSC_IN.Mode=HSE-External-Oscillator
PH0\ -\ OSC_IN.Signal=RCC_OSC_IN
PH1\ -\ OSC_OUT.Mode=HSE-External-Oscillator
PH1\ -\ OSC_OUT.Signal=RCC_OSC_OUT
RCC.HSE_VALUE=12000000
RCC.SYSCLKFreq_VALUE=100000000
RCC.SYSCLKSource=RCC_SYSCLKSOURCE_PLLCLK
board=custom

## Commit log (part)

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2026-06-15 Remove DS Store
2026-06-15 Added .gitignore
2026-06-19 testicles
2026-06-19 PCB uploading
2026-06-19 Giving all info for PCB
2026-06-19 Back to normal
2026-06-19 trying diff account
2026-06-19 Worked on LoRa and APRS
2026-06-20 Added 4.1V rail for APRS
2026-06-20 APRS work - MIC_IN pin left
2026-06-20 MCU sheet initial draft
2026-06-21 Added CS pins for SPI and hierarchical labels to MCU sheet
2026-06-21 Add STM32 firmware directory
2026-06-21 Add Directory for Raspberry Pi Software
2026-06-26 Standardized power symbols, added microSD sheet, and standardized hierarchical labels
2026-06-29 schematic
2026-06-30 Finished GPS
2026-06-30 Tidied some labels up
2026-06-30 adding IMU footprint+symbol
